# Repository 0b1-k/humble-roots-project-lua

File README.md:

**Summary**

The Humble Roots Project is a grow room automation control system designed for stable non-stop operation. It is managed through a single configuration file and can communicate with an administrator over SMS text messages. Data visualization is provided in the form of Grafana dashboards powered by InfluxDB.

**Dependencies**

Any platform capable of running Lua + sockets + file system support. Tested under Ubuntu 16, 17, 18+ and Raspbian.

***CMake***

```
sudo apt-get install cmake build-essential
```

***Git***

```
sudo apt-get install git
```

***LuaDist***

Install [LuaDist](http://luadist.org/) in the home folder.

***Humble Roots Project***

```
cd ~
git clone https://github.com/fabienroyer/humble-roots-project-lua.git
cd humble-roots-project-lua
cp -R * ~/LuaDist/share

# Compile the Serial Communication Library
cd ~/LuaDist/share/lua-serial
make

# Copy the library to the project folder. For 32-bit platforms:
cp ./build/lin32/libserial.so ~/LuaDist/share/weed
# or 64-bit platforms
cp ./build/lin64/libserial.so ~/LuaDist/share/weed

# Compile the SMS PDU encoding / decoding library
cd ~/LuaDist/share/smspdu
make

# Copy the library to the project folder. For 32-bit platforms
cp ./build/lin32/smspdu.so ~/LuaDist/share/weed
# or 64-bit platforms
cp ./build/lin64/smspdu.so ~/LuaDist/share/weed

# Copy the template config file to a usable .toml config file
cd ~/LuaDist/share/weed/config
mv config.tpl config.toml
cd ..
# Start the project
./../../bin/lua control.lua
```

On startup, the project will show a console output like this:

```
[TRACE 14:15:30] ./replay.lua:14: Replay data lines: 713
[INFO  14:15:30] control.lua:178: The Humble Roots Project
[INFO  14:15:30] control.lua:179: 
			                  |
			                 |.|
			                 |.|
			                |\./|
			                |\./|
			.               |\./|               .
			 \^.\          |\\.//|          /.^/
			  \--.|\       |\\.//|       /|.--/
			    \--.| \    |\\.//|    / |.--/
			     \---.|\    |\./|    /|.---/
			        \--.|\  |\./|  /|.--/
			           \ .\  |.|  /. /
			 _ -_^_^_^_-  \ \\ // /  -_^_^_^_- _
			   - -/_/_/- ^ ^  |  ^ ^ -\_\_\- -
					  	|

[INFO  14:15:30] control.lua:180: Copyright (c) 2017 Fabien Royer
[INFO  14:15:30] control.lua:185: Gateway started
[INFO  14:15:30] ./listener.lua:17: TCP listener @ ::1:42024
[DEBUG 14:15:31] control.lua:172: Replay node=2&rssi=-43&t=srh&bat=4.77&low=0&pwr=1&p=1
[DEBUG 14:15:32] control.lua:172: Replay node=20&rssi=-31&t=rly&bat=5.00&low=0&pwr=1&r=4&s=1
[DEBUG 14:15:33] control.lua:172: Replay node=20&rssi=-31&t=rly&bat=5.00&low=0&pwr=1&r=5&s=1
[DEBUG 14:15:34] control.lua:172: Replay node=20&rssi=-30&t=rly&bat=5.00&low=0&pwr=1&r=5&s=1
[DEBUG 14:15:35] control.lua:172: Replay node=40&rssi=-44&t=clm&bat=3.78&low=0&pwr=0&tmp=24.58&rh=55
...
```

***InfluxDB***

All sensor data is logged to [influxdb](https://influxdata.com/time-series-platform/influxdb/).
Once influxdb is installed, create a 'sensors' and an 'events' database, then enable influxdb logging in ./config/config.toml. See /weed/config/influxdb-udp.conf for a ready to use config snippet for communicating with InfluxDB over UDP (recommended over HTTP).

***Grafana***

Uses Grafana to plot sensor data. Once Grafana is installed, configure it to use the Influxdb instance previously installed and import the
Humble Roots Project dashboard from ./dashboard/grafana/Lab.json.

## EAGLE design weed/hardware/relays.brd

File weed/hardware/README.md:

The Humble Roots Project requires six power relays and one solenoid.
These parts can be obtained as off the shelf components are they can be
built using the provided schematics.

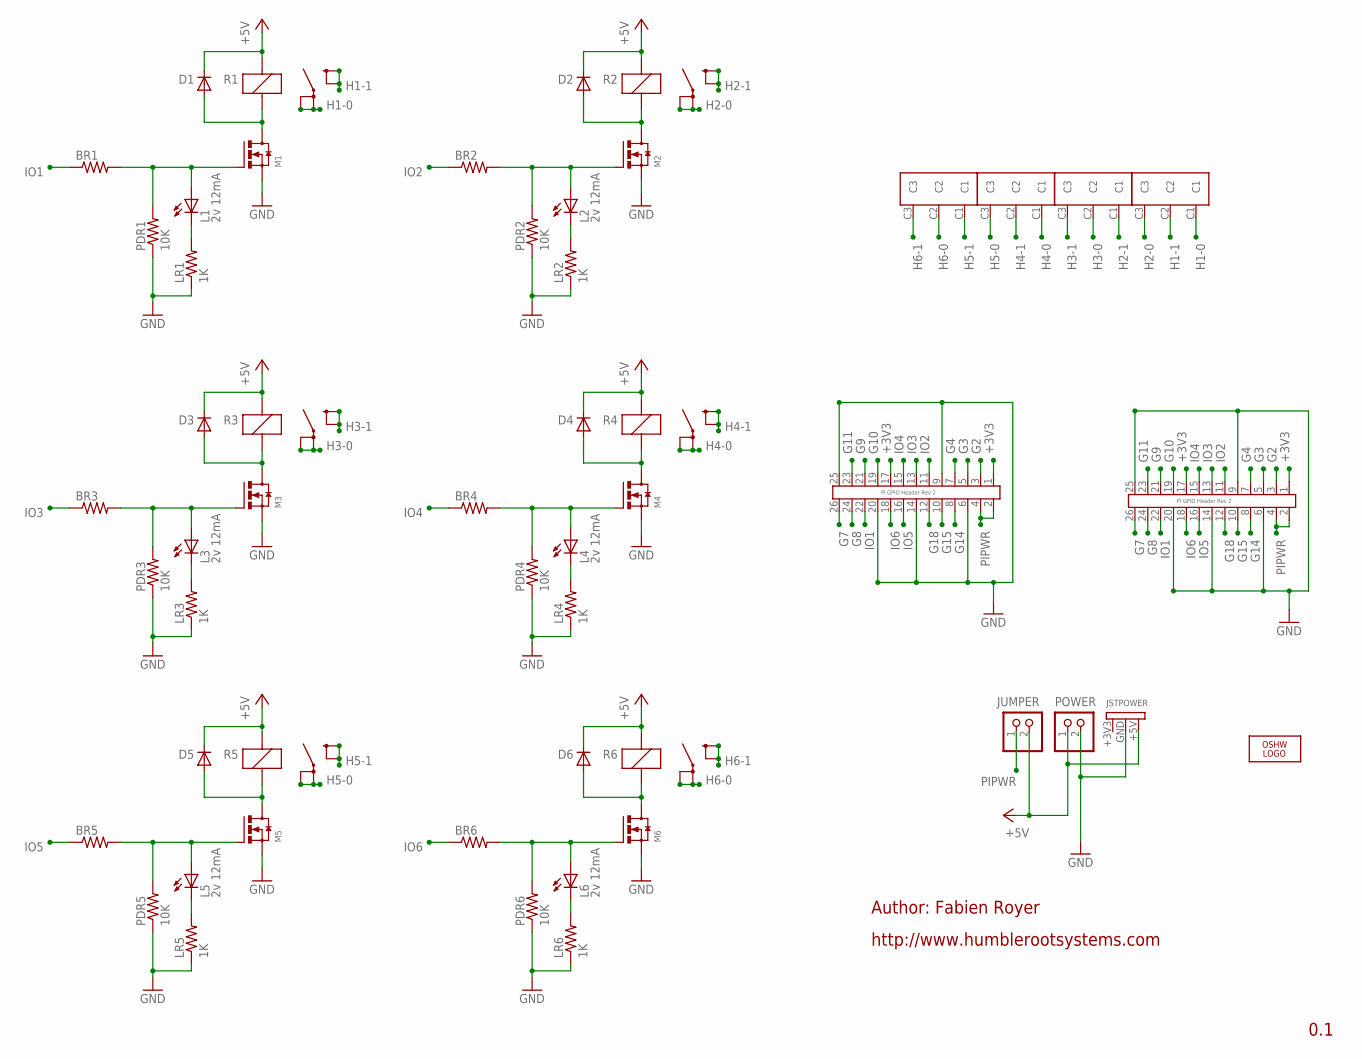
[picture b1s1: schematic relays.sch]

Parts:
BR1, BR2, BR3, BR4, BR5, BR6: R-US_0207/10; 0207/10
D1, D2, D3, D4, D5, D6: 1N4004; DO41-10
JSTPOWER: JST_PH_3_POSITIONS_TOP_ENTRY_THROUGH_HOLE
JUMPER: 5V; 1X02
L1, L2, L3, L4, L5, L6: 2v 12mA; LED3MM
LOGO1: OSHW_LOGO_6MILX0200-NT; OSHW_6X200_NOTEXT
LR1, LR2, LR3, LR4, LR5, LR6: 1K; 0207/10
M1, M2, M3, M4, M5, M6: FAIRCHILD_2N700X_N-CHANNEL_MOSFET_TO92; FAIRCHILD_2N700X_TO92
PDR1, PDR2, PDR3, PDR4, PDR5, PDR6: 10K; 0207/10
POWER: 5V; 1X02
R1, R2, R3, R4, R5, R6: SCHRACK_POWER_PCB_RELAY_RZ_16A_NO; SCHRACK_POWER_PCB_RELAY_RZ_16A
U$5, U$6: PI_GPIO_13X2_PIN_HEADER; PIN_HEADER_13X2_POSITIONS_DIL
WC1, WC2, WC3, WC4: PHOENIX_WIRE_CONTACT_3_POSITIONS_GENERIC

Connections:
+3V3: U$5.1 (P1_3V3), U$5.17 (P17_3V3), U$6.1 (P1_3V3), U$6.17 (P17_3V3)
+5V: D1.C, D2.C, D3.C, D4.C, D5.C, D6.C, JSTPOWER.+5V, JUMPER.2, POWER.1, R1.COIL_A1, R2.COIL_A1, R3.COIL_A1, R4.COIL_A1, R5.COIL_A1, R6.COIL_A1
G2: U$5.3 (P3_GPIO2_SDA), U$6.3 (P3_GPIO2_SDA)
G3: U$5.5 (P5_GPIO3_SCL), U$6.5 (P5_GPIO3_SCL)
G4: U$5.7 (P7_GPIO4), U$6.7 (P7_GPIO4)
G7: U$5.26 (P26_GPIO7_SPI0_CE1), U$6.26 (P26_GPIO7_SPI0_CE1)
G8: U$5.24 (P24_GPIO8_SPI0_CE0), U$6.24 (P24_GPIO8_SPI0_CE0)
G9: U$5.21 (P21_GPIO9_SPI0_MISO), U$6.21 (P21_GPIO9_SPI0_MISO)
G10: U$5.19 (P19_GPIO10_SPI0_MOSI), U$6.19 (P19_GPIO10_SPI0_MOSI)
G11: U$5.23 (P23_GPIO11_SPI0_SCLK), U$6.23 (P23_GPIO11_SPI0_SCLK)
G14: U$5.8 (P8_GPIO14_UART0_TXD), U$6.8 (P8_GPIO14_UART0_TXD)
G15: U$5.10 (P10_GPIO15_UART0_RXD), U$6.10 (P10_GPIO15_UART0_RXD)
G18: U$5.12 (P12_GPIO18), U$6.12 (P12_GPIO18)
GND: JSTPOWER.GND, LR1.1, LR2.1, LR3.1, LR4.1, LR5.1, LR6.1, M1.S (SOURCE), M2.S (SOURCE), M3.S (SOURCE), M4.S (SOURCE), M5.S (SOURCE), M6.S (SOURCE), PDR1.1, PDR2.1, PDR3.1, PDR4.1, PDR5.1, PDR6.1, POWER.2, U$5.6 (P6_GND), U$5.9 (P9_GND), U$5.14 (P14_GND), U$5.20 (P20_GND), U$5.25 (P25_GND), U$6.6 (P6_GND), U$6.9 (P9_GND), U$6.14 (P14_GND), U$6.20 (P20_GND), U$6.25 (P25_GND)
H1-0: R1.11A_LOAD, R1.11B_LOAD, WC1.C1
H1-1: R1.14A_LOAD, R1.14B_LOAD, WC1.C2
H2-0: R2.11A_LOAD, R2.11B_LOAD, WC1.C3
H2-1: R2.14A_LOAD, R2.14B_LOAD, WC2.C1
H3-0: R3.11A_LOAD, R3.11B_LOAD, WC2.C2
H3-1: R3.14A_LOAD, R3.14B_LOAD, WC2.C3
H4-0: R4.11A_LOAD, R4.11B_LOAD, WC3.C1
H4-1: R4.14A_LOAD, R4.14B_LOAD, WC3.C2
H5-0: R5.11A_LOAD, R5.11B_LOAD, WC3.C3
H5-1: R5.14A_LOAD, R5.14B_LOAD, WC4.C1
H6-0: R6.11A_LOAD, R6.11B_LOAD, WC4.C2
H6-1: R6.14A_LOAD, R6.14B_LOAD, WC4.C3
IO1: BR1.1, U$5.22 (P22_GPIO25), U$6.22 (P22_GPIO25)
IO2: BR2.1, U$5.11 (P11_GPIO17), U$6.11 (P11_GPIO17)
IO3: BR3.1, U$5.13 (P13_GPIO27), U$6.13 (P13_GPIO27)
IO4: BR4.1, U$5.15 (P15_GPIO22), U$6.15 (P15_GPIO22)
IO5: BR5.1, U$5.16 (P16_GPIO23), U$6.16 (P16_GPIO23)
IO6: BR6.1, U$5.18 (P18_GPIO24), U$6.18 (P18_GPIO24)
unnamed: L1.K (C), LR1.2
unnamed: BR2.2, L2.A, M2.G (GATE), PDR2.2
unnamed: L2.K (C), LR2.2
unnamed: D1.A, M1.D (DRAIN), R1.COIL_A2
unnamed: D2.A, M2.D (DRAIN), R2.COIL_A2
unnamed: BR1.2, L1.A, M1.G (GATE), PDR1.2
unnamed: BR3.2, L3.A, M3.G (GATE), PDR3.2
unnamed: L3.K (C), LR3.2
unnamed: D3.A, M3.D (DRAIN), R3.COIL_A2
unnamed: BR4.2, L4.A, M4.G (GATE), PDR4.2
unnamed: L4.K (C), LR4.2
unnamed: D4.A, M4.D (DRAIN), R4.COIL_A2
unnamed: BR5.2, L5.A, M5.G (GATE), PDR5.2
unnamed: L5.K (C), LR5.2
unnamed: D5.A, M5.D (DRAIN), R5.COIL_A2
unnamed: BR6.2, L6.A, M6.G (GATE), PDR6.2
unnamed: L6.K (C), LR6.2
unnamed: D6.A, M6.D (DRAIN), R6.COIL_A2
PIPWR: JUMPER.1, U$5.2 (P2_5V), U$5.4 (P4_5V), U$6.2 (P2_5V), U$6.4 (P4_5V)

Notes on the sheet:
0.1
Author: Fabien Royer
http://www.humblerootsystems.com

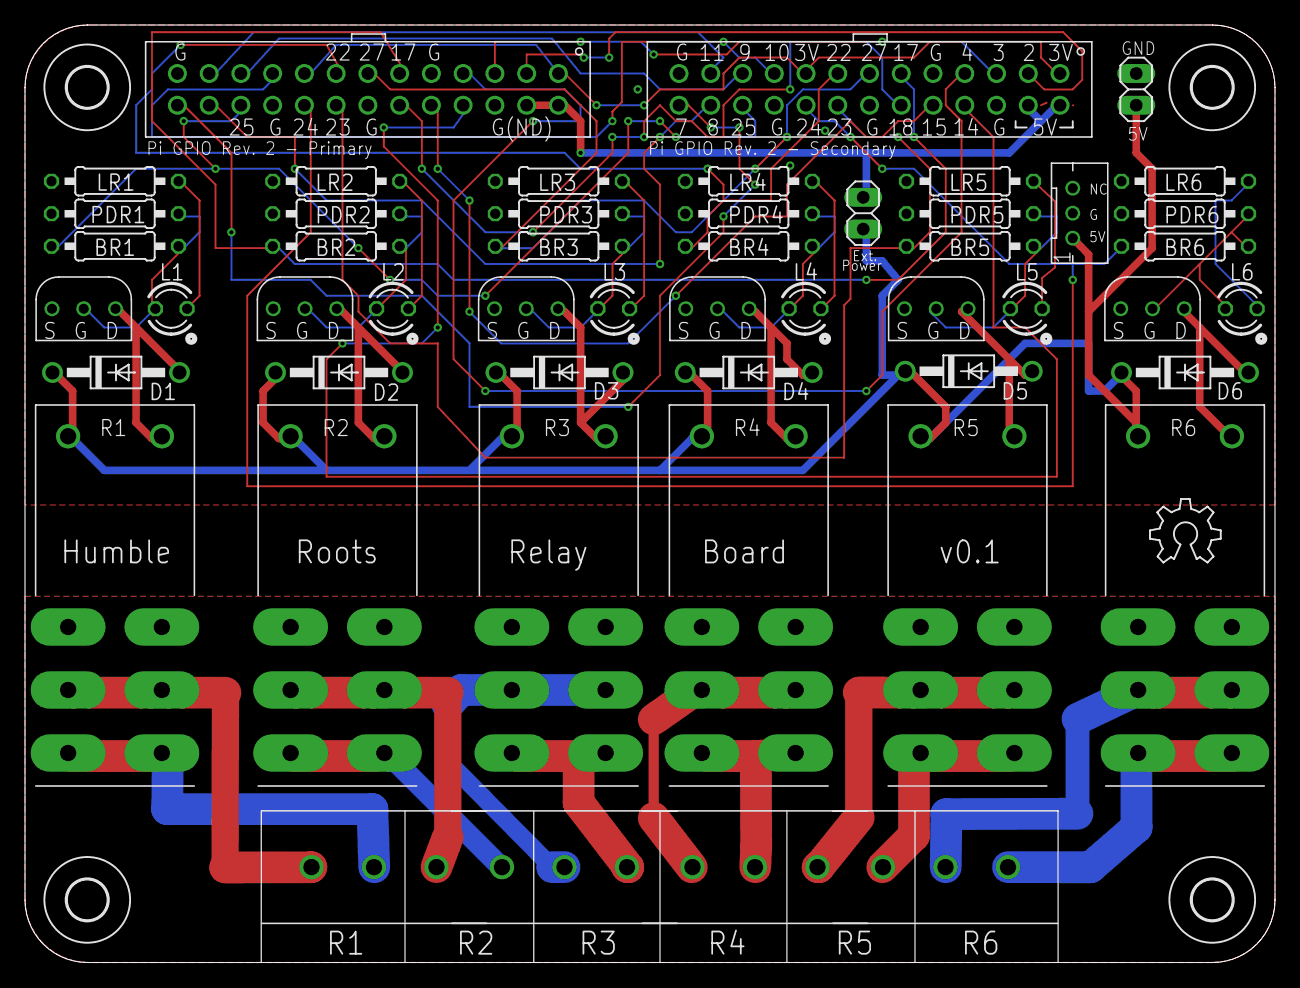
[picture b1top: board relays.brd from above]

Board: 2 copper layers, 100.0 x 75.0 mm, 56 parts (0 on the bottom side), 51 nets.

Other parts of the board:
U$1, U$2, U$3, U$4: 3,2

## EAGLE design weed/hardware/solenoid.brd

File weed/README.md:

# The Humble Roots Project (v1.0)
**Home Automation Applied To Medical Cannabis Cultivation**

The *Humble Roots Project* is a grow room automation system designed to meet indoor cannabis horticulture
challenges using open software, open hardware and readily available consumer appliances. The project
blends these elements together into an inexpensive, reliable, automated system, with a focus
on sustainability.

For in-depth details about the project, check out the [project documentation](./docs/HumbleRootsProject.pdf).

This version of the project is a complete Lua re-write of the former Python codebase.
Lua was found to provide greater reliability for long-running processes. It also takes far less resources than the 
Python implementation and is ideal on low-power systems such as the Raspberry Pi.
This implementation is single-threaded to prevent potential deadlocks and race-conditions.

**Plant Growth Timelapse**

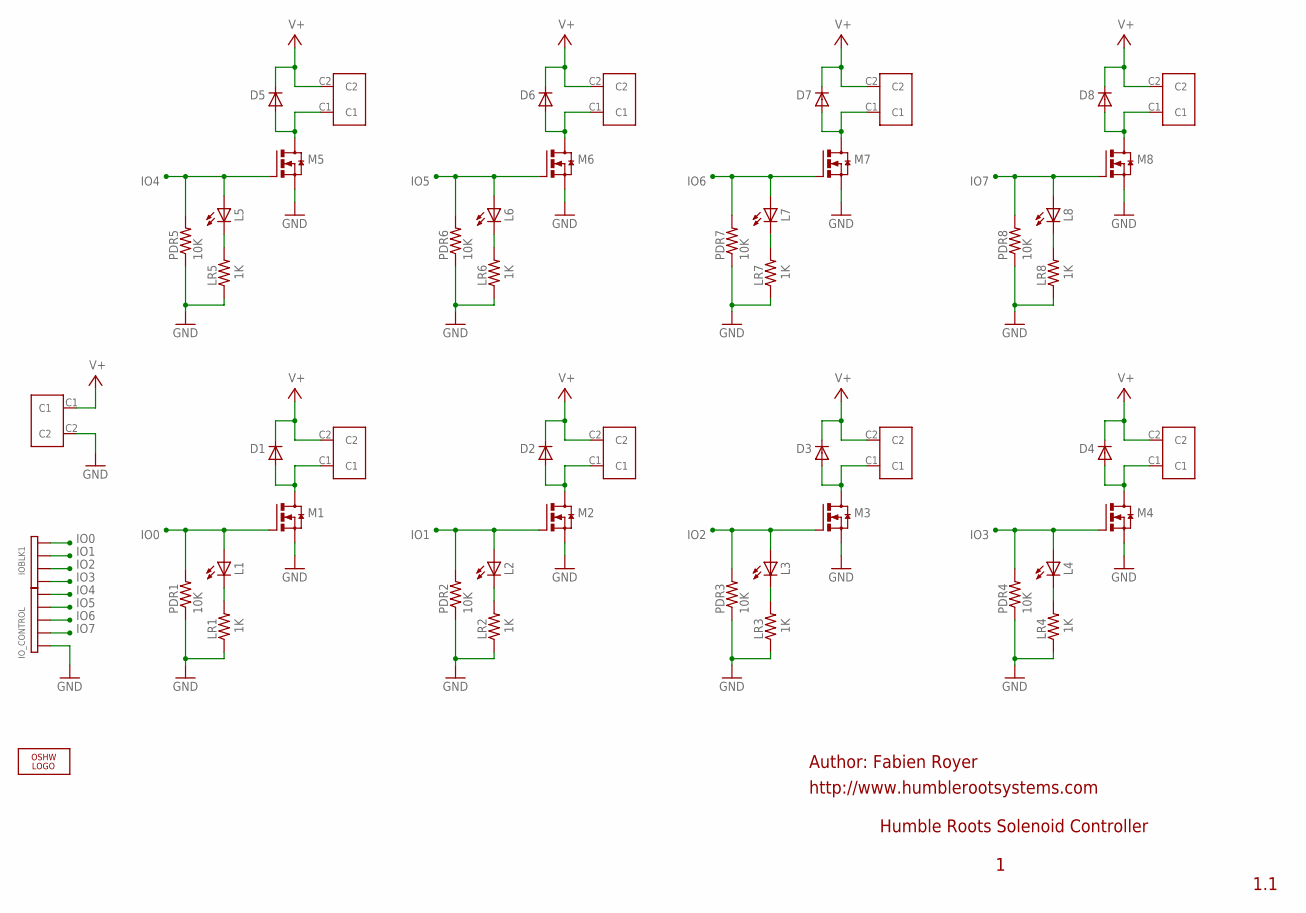
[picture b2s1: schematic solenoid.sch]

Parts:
D1, D2, D3, D4, D5, D6, D7, D8: 1N4004; DO41-10
IOBLK1: PIN_HEADER_4_POSITIONS
IO_CONTROL: PIN_HEADER_5_POSITIONS
L1, L2, L3, L4, L5, L6, L7, L8: 2v 12mA; LED3MM
LOGO1: OSHW_LOGO_6MILX0200-NT; OSHW_6X200_NOTEXT
LR1, LR2, LR3, LR4, LR5, LR6, LR7, LR8: 1K; 0207/10
M1, M2, M3, M4, M5, M6, M7, M8: INTERNATIONAL_RECTIFIER_IRLB8721PBF; TO220ABS
PDR1, PDR2, PDR3, PDR4, PDR5, PDR6, PDR7, PDR8: 10K; 0207/10
POWER: PHOENIX_WIRE_CONTACT_2_POSITIONS_GENERIC
V1, V2, V3, V4, V5, V6, V7, V8: PHOENIX_WIRE_CONTACT_2_POSITIONS_GENERIC

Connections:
GND: IO_CONTROL.5, LR1.1, LR2.1, LR3.1, LR4.1, LR5.1, LR6.1, LR7.1, LR8.1, M1.3 (SOURCE), M2.3 (SOURCE), M3.3 (SOURCE), M4.3 (SOURCE), M5.3 (SOURCE), M6.3 (SOURCE), M7.3 (SOURCE), M8.3 (SOURCE), PDR1.1, PDR2.1, PDR3.1, PDR4.1, PDR5.1, PDR6.1, PDR7.1, PDR8.1, POWER.C2
IO0: IOBLK1.1, L1.A, M1.1 (GATE), PDR1.2
IO1: IOBLK1.2, L2.A, M2.1 (GATE), PDR2.2
IO2: IOBLK1.3, L3.A, M3.1 (GATE), PDR3.2
IO3: IOBLK1.4, L4.A, M4.1 (GATE), PDR4.2
IO4: IO_CONTROL.1, L5.A, M5.1 (GATE), PDR5.2
IO5: IO_CONTROL.2, L6.A, M6.1 (GATE), PDR6.2
IO6: IO_CONTROL.3, L7.A, M7.1 (GATE), PDR7.2
IO7: IO_CONTROL.4, L8.A, M8.1 (GATE), PDR8.2
unnamed: L1.K (C), LR1.2
unnamed: L2.K (C), LR2.2
unnamed: D2.A, M2.2 (DRAIN), V2.C1
unnamed: L3.K (C), LR3.2
unnamed: D1.A, M1.2 (DRAIN), V1.C1
unnamed: D3.A, M3.2 (DRAIN), V3.C1
unnamed: L4.K (C), LR4.2
unnamed: D4.A, M4.2 (DRAIN), V4.C1
unnamed: L5.K (C), LR5.2
unnamed: D5.A, M5.2 (DRAIN), V5.C1
unnamed: L6.K (C), LR6.2
unnamed: D6.A, M6.2 (DRAIN), V6.C1
unnamed: L7.K (C), LR7.2
unnamed: D7.A, M7.2 (DRAIN), V7.C1
unnamed: L8.K (C), LR8.2
unnamed: D8.A, M8.2 (DRAIN), V8.C1
V+: D1.C, D2.C, D3.C, D4.C, D5.C, D6.C, D7.C, D8.C, POWER.C1, V1.C2, V2.C2, V3.C2, V4.C2, V5.C2, V6.C2, V7.C2, V8.C2

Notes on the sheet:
Humble Roots Solenoid Controller
1.1
Author: Fabien Royer
http://www.humblerootsystems.com

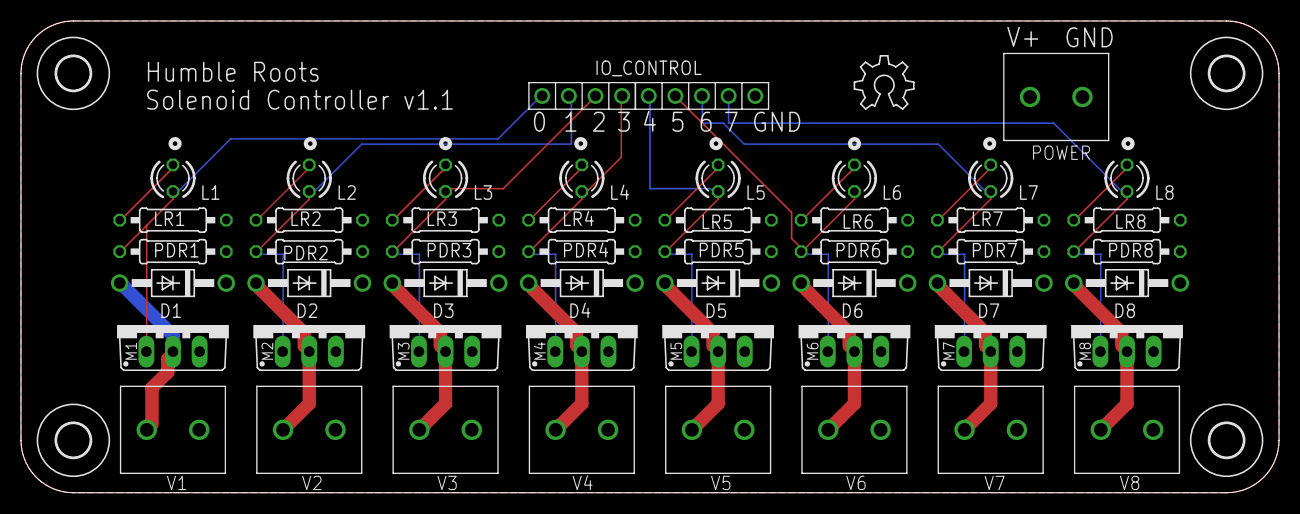
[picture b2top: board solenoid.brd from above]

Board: 2 copper layers, 120.0 x 45.0 mm, 56 parts (0 on the bottom side), 26 nets.

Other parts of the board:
U$1, U$2, U$3, U$4: 3,2

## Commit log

2016-08-25 compressed into hardware.zip
2016-08-25 compressed hardware designs and case
2016-08-27 fix to enalbe data replay
2016-08-27 fix typo
2016-08-27 install
2016-08-27 typos
2016-08-28 obsolete
2016-08-28 typo
2016-08-28 update architecture drawing
2016-08-28 outdated
2016-08-28 removed
2016-10-10 fix sensor <-> rule mismatch
2016-10-10 fix pending command removal and logging
2016-10-10 add tracing
2016-10-10 fix soil graph label
2016-10-16 fix bug writing to file
2016-10-16 gateway retry logic simplification
2016-10-16 latest
2016-10-17 added plant.top measurement to soil RH(%)
2016-10-17 removed useless dependencies
2016-10-17 added plant.top node
2016-10-17 added plant.top to rssi graph
2016-10-23 getopt as a module
2016-10-23 clean-up (wip)
2016-10-23 clean-up
2016-10-23 device command cleanup
2016-10-23 shell command clean-up
2016-10-23 command format clean-up
2016-10-23 default log location
2016-10-23 add days of week to time conditions
2016-10-23 fix detect restart on config change in replay mode
2016-10-23 add method to determine that the gateway stopped
2016-10-23 default command support
2016-10-23 debugger call removed
2016-10-23 updated to match config.tpl
2016-10-23 add day of week support to time-based rules
2016-10-23 larger data set
2016-10-23 bug fix
2016-10-24 fix time-based processing + rule tracing
2016-10-24 improved tracing
2016-10-24 fix default rule firing for invalid sensor
    still need to handle mixed nodes of same type bug.
2016-11-06 fix error msg format
2016-11-13 add event logging to influxDB
2016-11-13 add log + alerts panel
2016-11-13 add log + alerts screenshot
2016-11-13 fix warn on alert clearing
2016-11-28 refactor of json config and rule processing
    Enables multiple rules & optional default rule per sensor
2016-12-04 remove unnecessary dependency
2016-12-04 fix timer rules schema
2016-12-04 fix timer rules processing, gateway reset in replay mode
2016-12-04 fix shutdown() on stop()
    add method to reset stop event.
2016-12-04 remove unnecessary reference
2016-12-04 fix local variable
2016-12-04 fix missing nil check
2016-12-04 add config validation tool
2016-12-04 tweaks
2016-12-07 fix handling of "default" command rule
2016-12-07 fix process time rules first
2016-12-10 fix gateway startup / shutdown log level
2016-12-10 fix heartbeat recovery log level
2016-12-10 fix trace
2016-12-10 fix missing 'events' DB creation
2016-12-22 add LOG level
2016-12-22 add -w cli option
    Enables note-taking. Log messages are written to influxDB's 'events' db.
2016-12-22 add annotations query to overlay on graphs
2016-12-22 update screenshot
2016-12-25 add light power monitoring (lux) node
2016-12-25 fix spaces
2016-12-25 add optional reboot on excessive node timeout
2017-01-02 add lux meter arduino sketch
2017-01-12 add csv line parser
2017-01-12 add utility for writing events to influxDB from a data/time/text log in CSV format
2017-01-12 add drying template
2017-01-12 add grafana dashboard for drying + screenshot
2017-01-12 fix reset alerts on gateway restart
2017-01-12 fix reset all alerts on gateway restart
2017-01-15 add influxdb udp transport
2017-01-15 add influxdb udp transport support
    Ensures that http calls to the db won't hang and disrupt operations when
    the target influxdb is inaccessible.
2017-01-15 add influxdb udp transport support
2017-01-15 expected influxdb config for udp transport support
2017-01-15 fix influxdb.udp.enabled typo
2017-01-16 fix reset message body after retrieval
2017-01-17 add init/shutdown functions handling UDP socket creation/destruction
2017-01-22 add write to influxDB
2017-01-22 add tine precision + improved error reporting on failure
2017-01-22 add InfluxDB snapshot with sensor & event data
2017-01-22 add InfluxDB snapshot description
2017-01-22 update copyright info
2017-01-22 add AK-48 pics
2017-01-23 add retry object dump when an anomaly occurs
2017-01-28 fix improved alert messages
2017-01-28 fix initial install steps
2017-01-28 add alerts strings
2017-02-12 add message when missing config.json file
2017-02-12 update replay.txt dataset
2017-11-27 add .toml support
2017-11-27 add smspdu library (SMS message encoding/decoding)
2017-11-27 touched
2017-11-27 switch from .json to .toml config
2017-11-27 Refactor to support new rule format and indexing. Fixed shell input handling. Removed unnecessary tostring() calls.
2017-11-27 Removed unnecessary tostring() calls.
2017-11-27 Removed unnecessary tostring() calls. Removed serial delay.
2017-11-27 add self-contained SMS gateway
    Tested with Huawei BOLTZ 4G LTE modem
2017-11-27 Refactored according to new rule format. Fix 'all-day / 00:00-23:59' timing hole. Removed md5 dependency. Removed unnecessary tostring() calls.
2017-11-27 Fix report show index instead of name with relays/valves
2017-11-27 add AK-48 grow journal
2017-11-27 modem init + launch
2017-11-27 updated summary, dependencies, build steps.
2018-01-27 Copyright year update
2018-01-27 fix don't send the same command twice in a row
    fix rule off command ignored when default command defined
2018-02-04 add handling of default rules within rule blocks
    [control.climate.clm]
    [control.climate.clm.0]
    enabled = true
    value = "tmp"
    time = {from = "17:00", to = "05:00"}
    on = {op = ">=", setpoint = 23.0, cmd = "-n relay -r vent -s on"}
2018-02-05 fix timeout issue when sending multiple messages at the same time
    fix to ensure that storage memory used to send messages is always cleared before sending
2018-11-23 remove reset between commands
2018-11-23 updated to used compound rules
    add calibration offset
2018-11-23 update UDP config to match InfluxDB 1.7 settings
2018-11-23 use .toml config files
    fix for compound rules
    remove reset between shell commands
2018-11-23 no change
2018-11-23 test with latest Grafana version
2018-11-23 remove md5 dependency
    fix time gap between 23:59 and 00:00
    remove unnecessary tostring() calls
    ignore duplicate commands
    handle compound rules
    add sensor calibration offset
2018-12-09 fix detect and log out of sync configuration
2018-12-09 fix return early on peer name resolution failure
